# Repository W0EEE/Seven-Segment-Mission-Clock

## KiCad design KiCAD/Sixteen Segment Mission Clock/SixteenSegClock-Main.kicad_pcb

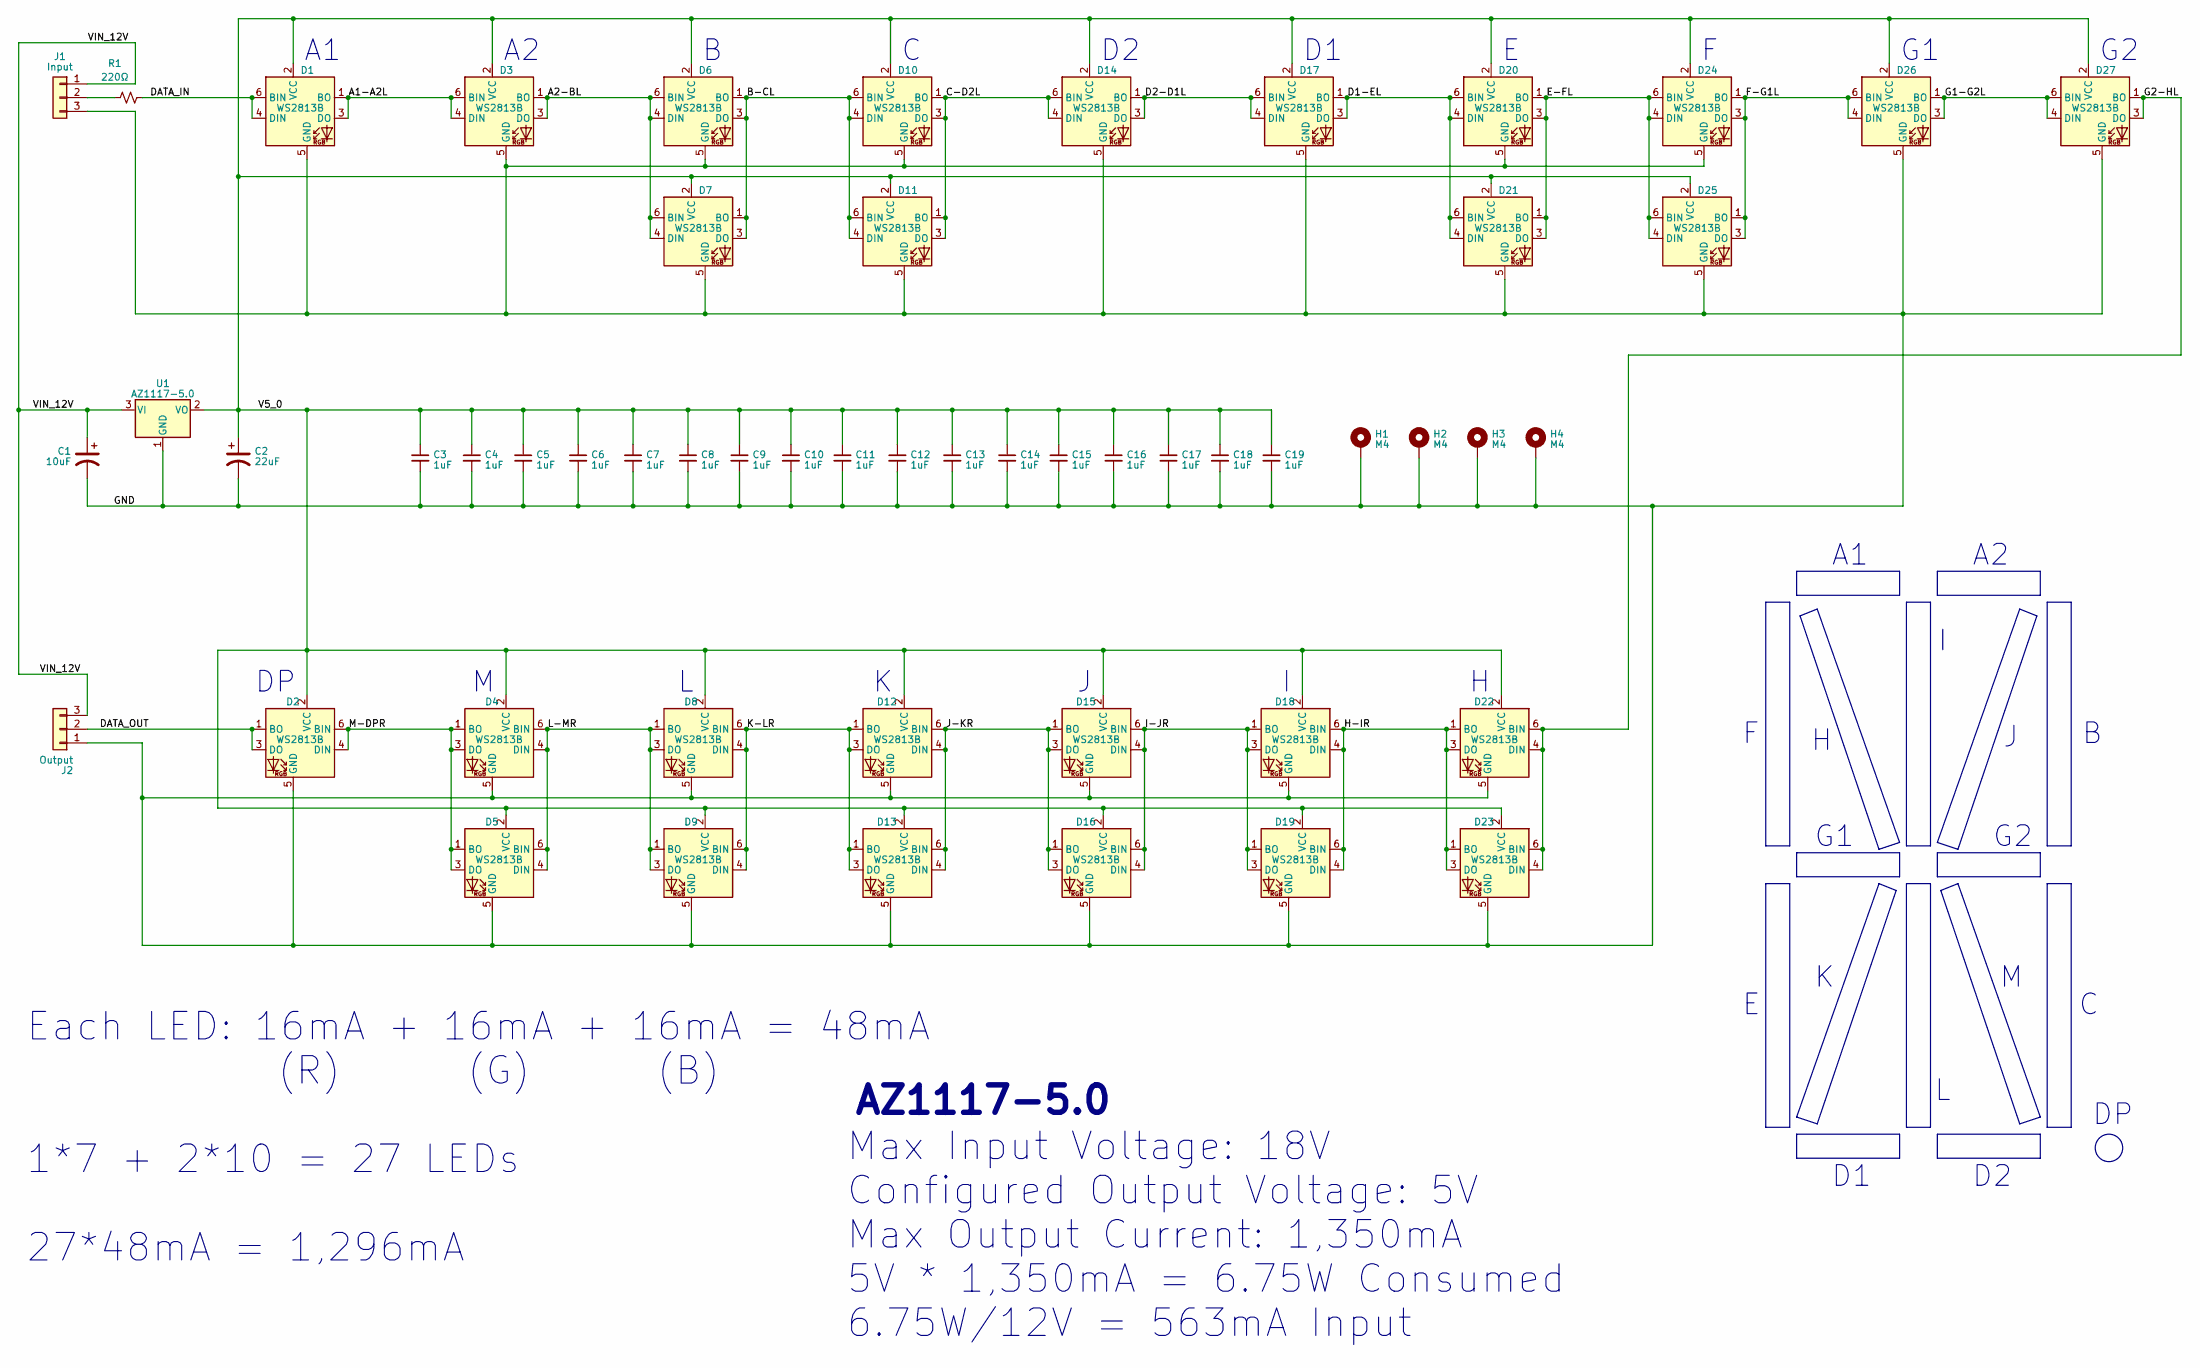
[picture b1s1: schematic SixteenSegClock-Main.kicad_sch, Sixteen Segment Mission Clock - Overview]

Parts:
C1: 10uF; C_0603_1608Metric_Pad1.08x0.95mm_HandSolder
C2: 22uF; C_0603_1608Metric_Pad1.08x0.95mm_HandSolder
C3, C4, C5, C6, C7, C8, C9, C10, C11, C12, C13, C14, C15, C16, C17, C18, C19: 1uF; C_0603_1608Metric_Pad1.08x0.95mm_HandSolder
D1, D2, D3, D4, D5, D6, D7, D8, D9, D10, D11, D12, D13, D14, D15, D16, D17, D18, D19, D20, D21, D22, D23, D24, D25, D26, D27: WS2813B; LED_WS2812_PLCC6_5.0x5.0mm_P1.6mm
H1, H2, H3, H4: M4; MountingHole_4.3mm_M4_DIN965_Pad
J1: Input; PinHeader_1x03_P2.54mm_Horizontal
J2: Output; PinHeader_1x03_P2.54mm_Horizontal
R1: 220Ω; R_0603_1608Metric_Pad0.98x0.95mm_HandSolder
U1: AZ1117-5.0; SOT-223-3_TabPin2

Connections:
/A1-A2L: D1.1 (BO), D1.3 (DO), D3.4 (DIN), D3.6 (BIN)
/A2-BL: D3.1 (BO), D3.3 (DO), D6.4 (DIN), D6.6 (BIN), D7.4 (DIN), D7.6 (BIN)
/B-CL: D6.1 (BO), D6.3 (DO), D7.1 (BO), D7.3 (DO), D10.4 (DIN), D10.6 (BIN), D11.4 (DIN), D11.6 (BIN)
/C-D2L: D10.1 (BO), D10.3 (DO), D11.1 (BO), D11.3 (DO), D14.4 (DIN), D14.6 (BIN)
/D1-EL: D17.1 (BO), D17.3 (DO), D20.4 (DIN), D20.6 (BIN), D21.4 (DIN), D21.6 (BIN)
/D2-D1L: D14.1 (BO), D14.3 (DO), D17.4 (DIN), D17.6 (BIN)
/DATA_IN: D1.4 (DIN), D1.6 (BIN), R1.2
/DATA_OUT: D2.1 (BO), D2.3 (DO), J2.2
/E-FL: D20.1 (BO), D20.3 (DO), D21.1 (BO), D21.3 (DO), D24.4 (DIN), D24.6 (BIN), D25.4 (DIN), D25.6 (BIN)
/F-G1L: D24.1 (BO), D24.3 (DO), D25.1 (BO), D25.3 (DO), D26.4 (DIN), D26.6 (BIN)
/G1-G2L: D26.1 (BO), D26.3 (DO), D27.4 (DIN), D27.6 (BIN)
/G2-HL: D22.4 (DIN), D22.6 (BIN), D23.4 (DIN), D23.6 (BIN), D27.1 (BO), D27.3 (DO)
/GND: C1.2, C2.2, C3.2, C4.2, C5.2, C6.2, C7.2, C8.2, C9.2, C10.2, C11.2, C12.2, C13.2, C14.2, C15.2, C16.2, C17.2, C18.2, C19.2, D1.5 (GND), D2.5 (GND), D3.5 (GND), D4.5 (GND), D5.5 (GND), D6.5 (GND), D7.5 (GND), D8.5 (GND), D9.5 (GND), D10.5 (GND), D11.5 (GND), D12.5 (GND), D13.5 (GND), D14.5 (GND), D15.5 (GND), D16.5 (GND), D17.5 (GND), D18.5 (GND), D19.5 (GND), D20.5 (GND), D21.5 (GND), D22.5 (GND), D23.5 (GND), D24.5 (GND), D25.5 (GND), D26.5 (GND), D27.5 (GND), H1.1, H2.1, H3.1, H4.1, J1.3, J2.1, U1.1 (GND)
/H-IR: D18.4 (DIN), D18.6 (BIN), D19.4 (DIN), D19.6 (BIN), D22.1 (BO), D22.3 (DO), D23.1 (BO), D23.3 (DO)
/I-JR: D15.4 (DIN), D15.6 (BIN), D16.4 (DIN), D16.6 (BIN), D18.1 (BO), D18.3 (DO), D19.1 (BO), D19.3 (DO)
/J-KR: D12.4 (DIN), D12.6 (BIN), D13.4 (DIN), D13.6 (BIN), D15.1 (BO), D15.3 (DO), D16.1 (BO), D16.3 (DO)
/K-LR: D8.4 (DIN), D8.6 (BIN), D9.4 (DIN), D9.6 (BIN), D12.1 (BO), D12.3 (DO), D13.1 (BO), D13.3 (DO)
/L-MR: D4.4 (DIN), D4.6 (BIN), D5.4 (DIN), D5.6 (BIN), D8.1 (BO), D8.3 (DO), D9.1 (BO), D9.3 (DO)
/M-DPR: D2.4 (DIN), D2.6 (BIN), D4.1 (BO), D4.3 (DO), D5.1 (BO), D5.3 (DO)
/V5_0: C2.1, C3.1, C4.1, C5.1, C6.1, C7.1, C8.1, C9.1, C10.1, C11.1, C12.1, C13.1, C14.1, C15.1, C16.1, C17.1, C18.1, C19.1, D1.2 (VCC), D2.2 (VCC), D3.2 (VCC), D4.2 (VCC), D5.2 (VCC), D6.2 (VCC), D7.2 (VCC), D8.2 (VCC), D9.2 (VCC), D10.2 (VCC), D11.2 (VCC), D12.2 (VCC), D13.2 (VCC), D14.2 (VCC), D15.2 (VCC), D16.2 (VCC), D17.2 (VCC), D18.2 (VCC), D19.2 (VCC), D20.2 (VCC), D21.2 (VCC), D22.2 (VCC), D23.2 (VCC), D24.2 (VCC), D25.2 (VCC), D26.2 (VCC), D27.2 (VCC), U1.2 (VO)
/VIN_12V: C1.1, J1.1, J2.3, U1.3 (VI)
unnamed: J1.2, R1.1

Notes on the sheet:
Max Input Voltage: 18V Configured Output Voltage: 5V Max Output Current: 1,350mA 5V * 1,350mA = 6.75W Consumed 6.75W/12V = 563mA Input
Each LED: 16mA + 16mA + 16mA = 48mA (R) (G) (B) 1*7 + 2*10 = 27 LEDs 27*48mA = 1,296mA
AZ1117-5.0

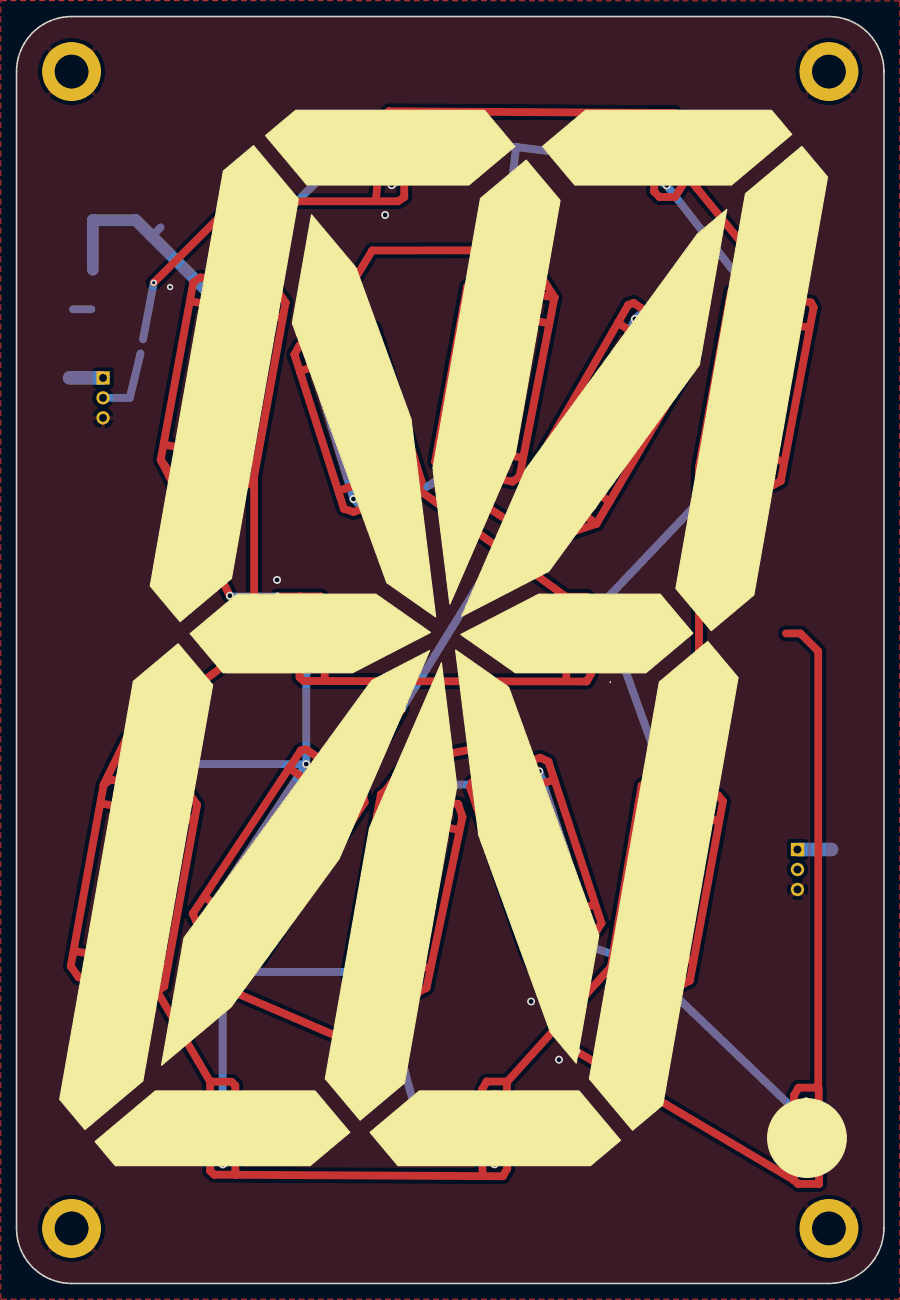
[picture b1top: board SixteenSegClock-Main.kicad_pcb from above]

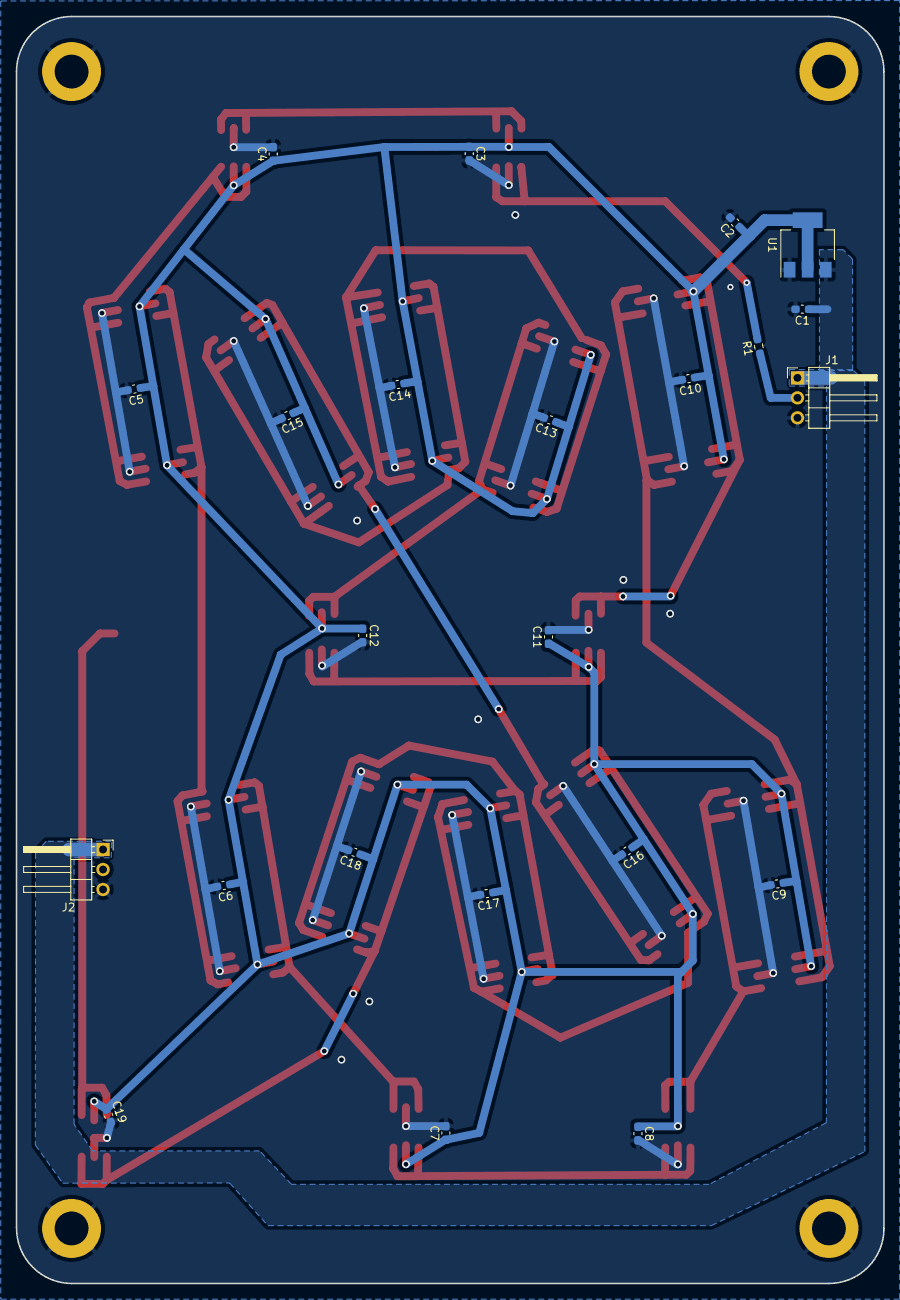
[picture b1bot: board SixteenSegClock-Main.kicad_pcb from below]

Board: 2 copper layers, 110.3 x 161.1 mm, 54 parts (23 on the bottom side), 22 nets.

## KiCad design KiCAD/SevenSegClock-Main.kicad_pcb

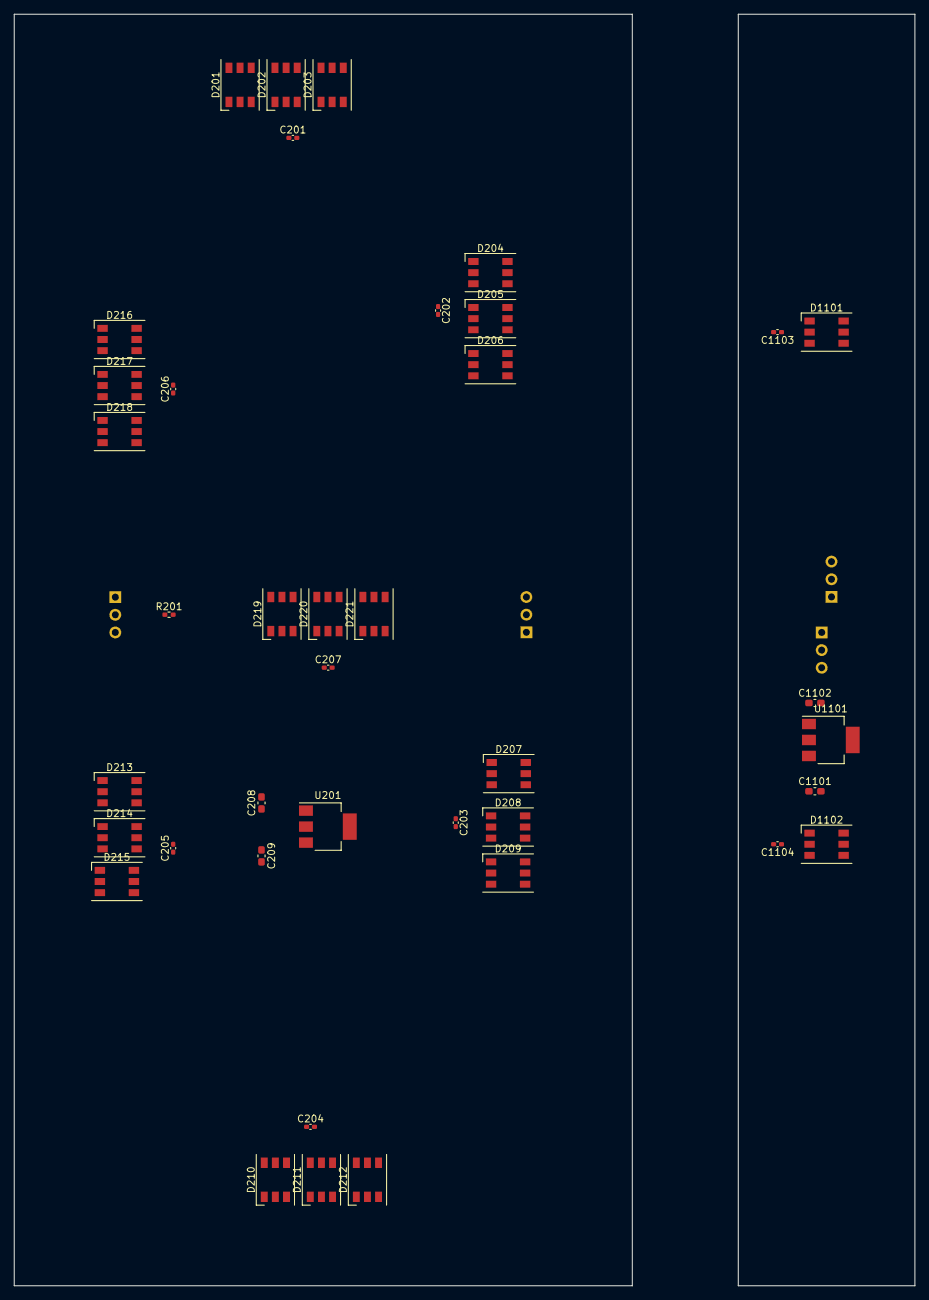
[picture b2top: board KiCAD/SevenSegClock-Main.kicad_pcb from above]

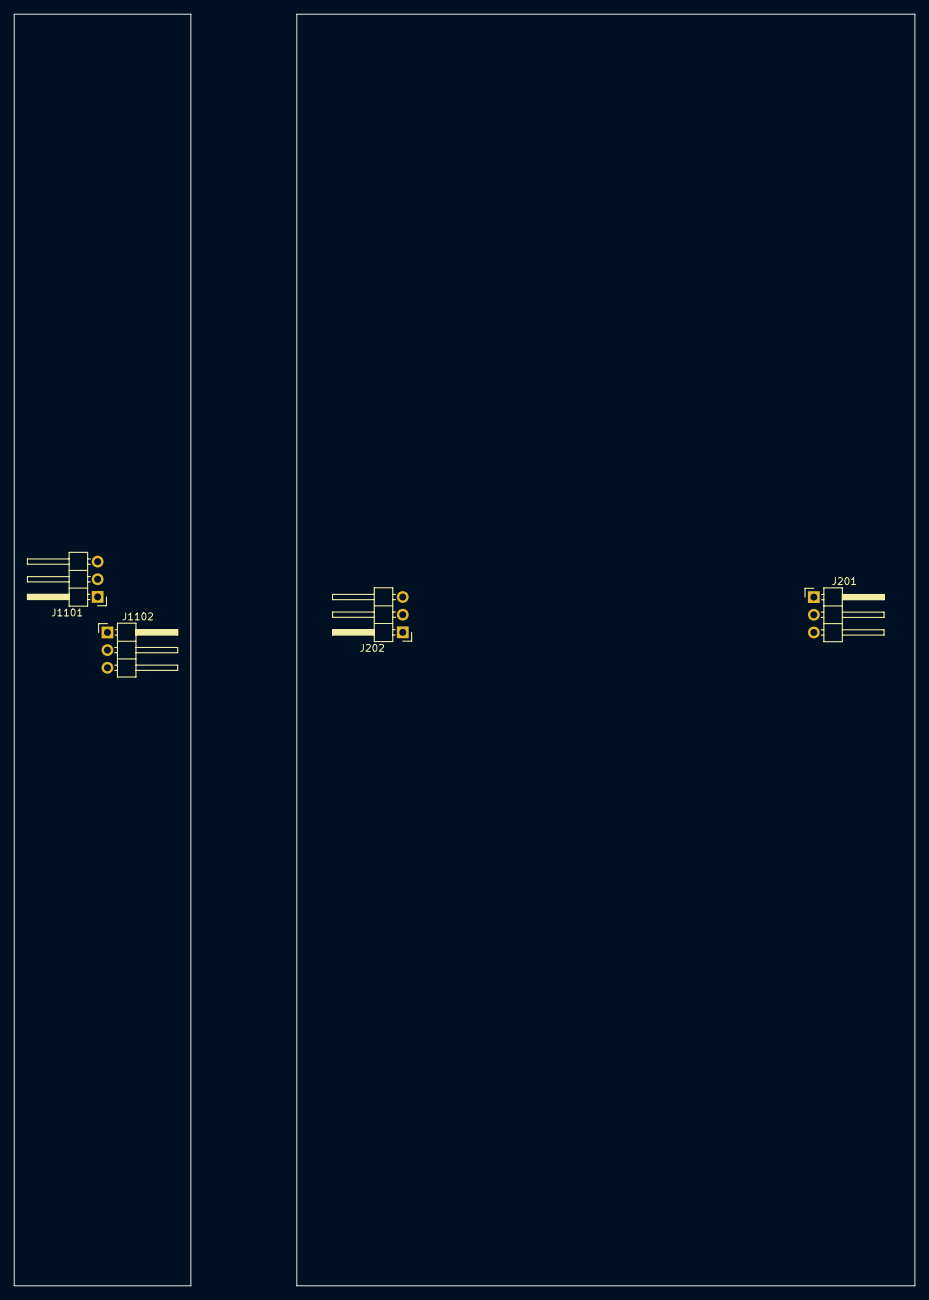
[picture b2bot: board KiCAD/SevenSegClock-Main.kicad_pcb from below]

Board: 2 copper layers, 129.5 x 182.9 mm, 43 parts (4 on the bottom side), 17 nets, no tracks yet.

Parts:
C201, C202, C203, C204, C205, C206, C207, C1103, C1104: 1uF; C_0402_1005Metric_Pad0.74x0.62mm_HandSolder
C208, C209, C1101, C1102: 10uF; C_0603_1608Metric_Pad1.08x0.95mm_HandSolder
D201, D202, D203, D204, D205, D206, D207, D208, D209, D210, D211, D212, D213, D214, D215, D216, D217, D218, D219, D220, D221, D1101, D1102: WS2813B; LED_WS2812_PLCC6_5.0x5.0mm_P1.6mm
J201: Input; PinHeader_1x03_P2.54mm_Horizontal
J202, J1101, J1102: Output; PinHeader_1x03_P2.54mm_Horizontal
R201: 220Ω; R_0402_1005Metric_Pad0.72x0.64mm_HandSolder
U201, U1101: AZ1117-5.0; SOT-223-3_TabPin2

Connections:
/Colon 1/DATA_IN: D1101.4 (DIN), D1101.6 (BIN), D1102.4 (DIN), D1102.6 (BIN), J1102.2
/Colon 1/DATA_OUT: D1101.1 (BO), D1101.3 (DO), D1102.1 (BO), D1102.3 (DO), J1101.2
/Colon 1/GND: C1101.2, C1102.2, C1103.2, C1104.2, D1101.5 (GND), D1102.5 (GND), J1101.3, J1102.3, U1101.1 (GND)
/Colon 1/V5_0: C1102.1, C1103.1, C1104.1, D1101.2 (VCC), D1102.2 (VCC), U1101.2 (VO)
/Colon 1/VIN_12V: C1101.1, J1101.1, J1102.1, U1101.3 (VI)
/Day 100s/A-B: D201.1 (BO), D201.3 (DO), D202.1 (BO), D202.3 (DO), D203.1 (BO), D203.3 (DO), D204.4 (DIN), D204.6 (BIN), D205.4 (DIN), D205.6 (BIN), D206.4 (DIN), D206.6 (BIN)
/Day 100s/B-C: D204.1 (BO), D204.3 (DO), D205.1 (BO), D205.3 (DO), D206.1 (BO), D206.3 (DO), D207.4 (DIN), D207.6 (BIN), D208.4 (DIN), D208.6 (BIN), D209.4 (DIN), D209.6 (BIN)
/Day 100s/C-D: D207.1 (BO), D207.3 (DO), D208.1 (BO), D208.3 (DO), D209.1 (BO), D209.3 (DO), D210.4 (DIN), D210.6 (BIN), D213.4 (DIN), D213.6 (BIN), D216.4 (DIN), D216.6 (BIN)
/Day 100s/D-E: D210.1 (BO), D210.3 (DO), D211.4 (DIN), D211.6 (BIN), D213.1 (BO), D213.3 (DO), D214.4 (DIN), D214.6 (BIN), D216.1 (BO), D216.3 (DO), D217.4 (DIN), D217.6 (BIN)
/Day 100s/DATA_IN: D201.4 (DIN), D201.6 (BIN), D202.4 (DIN), D202.6 (BIN), D203.4 (DIN), D203.6 (BIN), R201.2
/Day 100s/DATA_OUT: D219.1 (BO), D219.3 (DO), D220.1 (BO), D220.3 (DO), D221.1 (BO), D221.3 (DO), J202.2
/Day 100s/E-F: D211.1 (BO), D211.3 (DO), D212.4 (DIN), D212.6 (BIN), D214.1 (BO), D214.3 (DO), D215.4 (DIN), D215.6 (BIN), D217.1 (BO), D217.3 (DO), D218.4 (DIN), D218.6 (BIN)
/Day 100s/F-G: D212.1 (BO), D212.3 (DO), D215.1 (BO), D215.3 (DO), D218.1 (BO), D218.3 (DO), D219.4 (DIN), D219.6 (BIN), D220.4 (DIN), D220.6 (BIN), D221.4 (DIN), D221.6 (BIN)
/Day 100s/GND: C201.2, C202.2, C203.2, C204.2, C205.2, C206.2, C207.2, C208.2, C209.2, D201.5 (GND), D202.5 (GND), D203.5 (GND), D204.5 (GND), D205.5 (GND), D206.5 (GND), D207.5 (GND), D208.5 (GND), D209.5 (GND), D210.5 (GND), D211.5 (GND), D212.5 (GND), D213.5 (GND), D214.5 (GND), D215.5 (GND), D216.5 (GND), D217.5 (GND), D218.5 (GND), D219.5 (GND), D220.5 (GND), D221.5 (GND), J201.3, J202.3, U201.1 (GND)
/Day 100s/V5_0: C201.1, C202.1, C203.1, C204.1, C205.1, C206.1, C207.1, C208.1, D201.2 (VCC), D202.2 (VCC), D203.2 (VCC), D204.2 (VCC), D205.2 (VCC), D206.2 (VCC), D207.2 (VCC), D208.2 (VCC), D209.2 (VCC), D210.2 (VCC), D211.2 (VCC), D212.2 (VCC), D213.2 (VCC), D214.2 (VCC), D215.2 (VCC), D216.2 (VCC), D217.2 (VCC), D218.2 (VCC), D219.2 (VCC), D220.2 (VCC), D221.2 (VCC), U201.2 (VO)
/Day 100s/VIN_12V: C209.1, J201.1, J202.1, U201.3 (VI)
unnamed: J201.2, R201.1

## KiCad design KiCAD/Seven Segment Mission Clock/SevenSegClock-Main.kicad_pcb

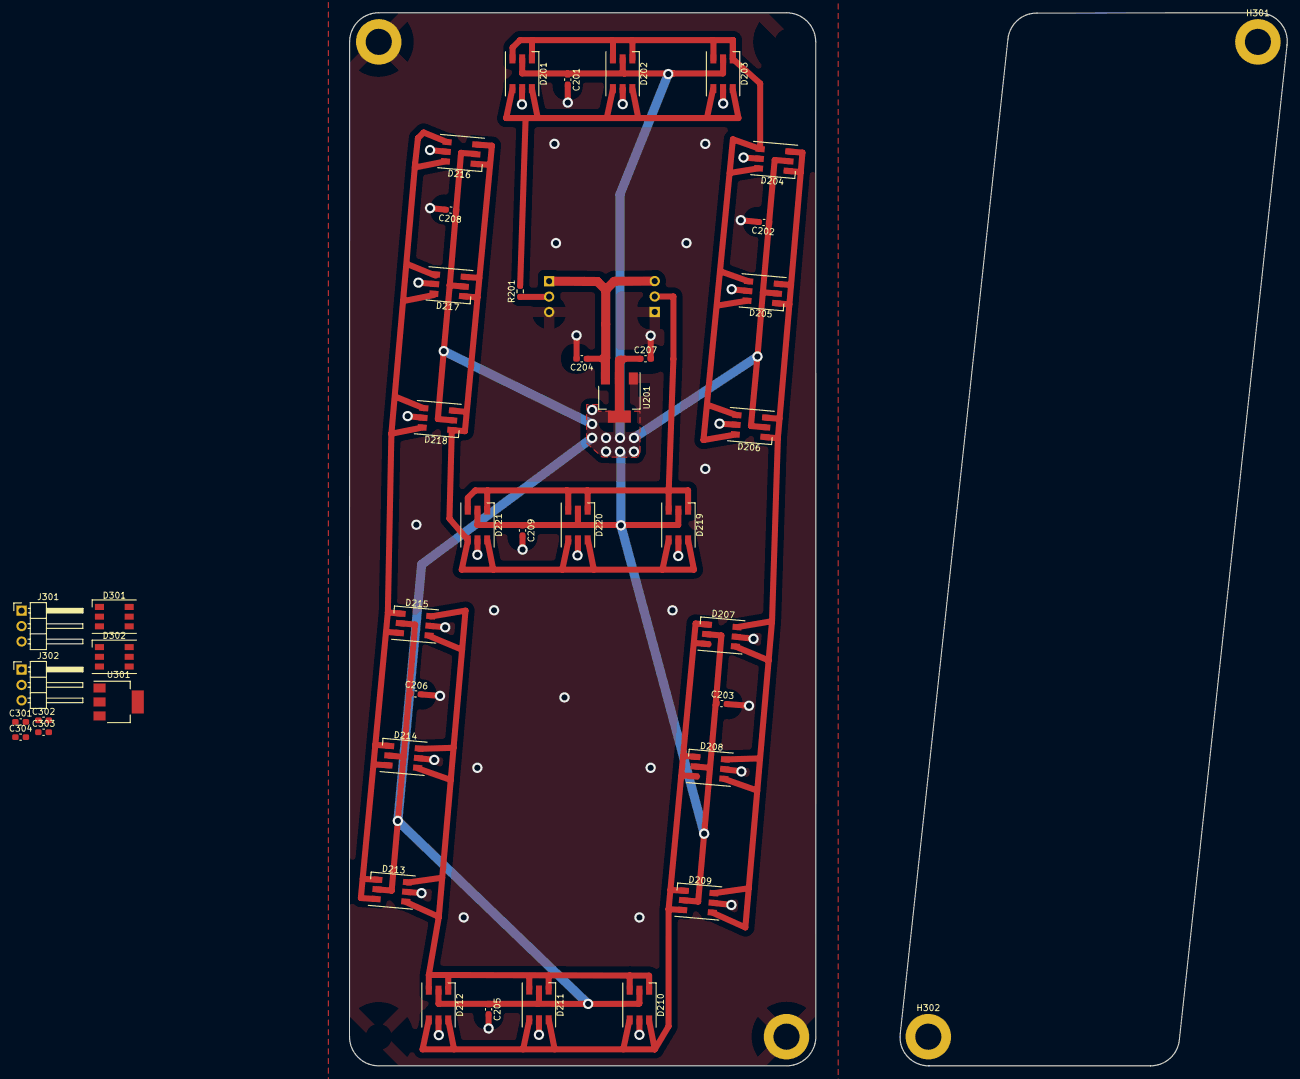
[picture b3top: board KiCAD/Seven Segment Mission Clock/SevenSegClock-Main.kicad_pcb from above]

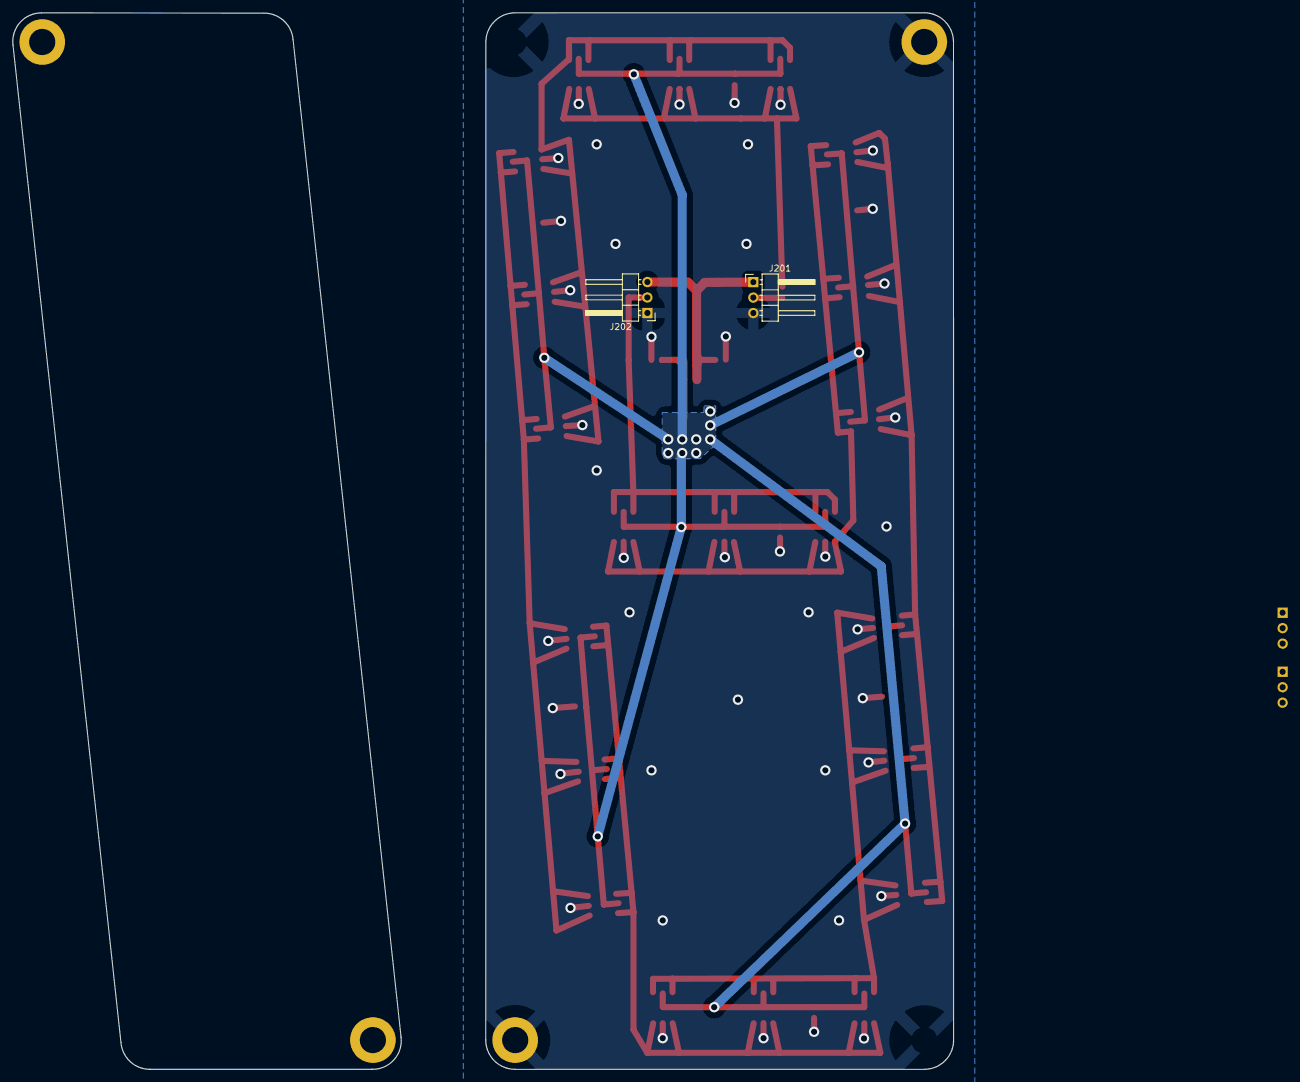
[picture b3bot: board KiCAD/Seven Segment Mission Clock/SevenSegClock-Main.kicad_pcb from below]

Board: 2 copper layers, 154.5 x 173.5 mm, 47 parts (2 on the bottom side), 17 nets.

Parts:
C201, C202, C203, C205, C206, C208, C209, C302, C303: 1uF; C_0603_1608Metric_Pad1.08x0.95mm_HandSolder
C204, C207, C301, C304: 10uF; C_0603_1608Metric_Pad1.08x0.95mm_HandSolder
D201, D202, D203, D204, D205, D206, D207, D208, D209, D210, D211, D212, D213, D214, D215, D216, D217, D218, D219, D220, D221, D301, D302: WS2813B; LED_WS2812_PLCC6_5.0x5.0mm_P1.6mm
H201, H202, H301, H302: M4; MountingHole_4.3mm_M4_DIN965_Pad
J201: Input; PinHeader_1x03_P2.54mm_Horizontal
J202, J301, J302: Output; PinHeader_1x03_P2.54mm_Horizontal
R201: 220Ω; R_0603_1608Metric_Pad0.98x0.95mm_HandSolder
U201, U301: AZ1117-5.0; SOT-223-3_TabPin2

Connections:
/Colon/DATA_IN: D301.4 (DIN), D301.6 (BIN), D302.4 (DIN), D302.6 (BIN), J301.2
/Colon/DATA_OUT: D301.1 (BO), D301.3 (DO), D302.1 (BO), D302.3 (DO), J302.2
/Colon/GND: C301.2, C302.2, C303.2, C304.2, D301.5 (GND), D302.5 (GND), H301.1, H302.1, J301.3, J302.3, U301.1 (GND)
/Colon/V5_0: C302.1, C303.1, C304.1, D301.2 (VCC), D302.2 (VCC), U301.2 (VO)
/Colon/VIN_12V: C301.1, J301.1, J302.1, U301.3 (VI)
/Seven Segment Digit/A-B: D201.1 (BO), D201.3 (DO), D202.1 (BO), D202.3 (DO), D203.1 (BO), D203.3 (DO), D204.4 (DIN), D204.6 (BIN), D205.4 (DIN), D205.6 (BIN), D206.4 (DIN), D206.6 (BIN)
/Seven Segment Digit/B-C: D204.1 (BO), D204.3 (DO), D205.1 (BO), D205.3 (DO), D206.1 (BO), D206.3 (DO), D207.4 (DIN), D207.6 (BIN), D208.4 (DIN), D208.6 (BIN), D209.4 (DIN), D209.6 (BIN)
/Seven Segment Digit/C-D: D207.1 (BO), D207.3 (DO), D208.1 (BO), D208.3 (DO), D209.1 (BO), D209.3 (DO), D210.4 (DIN), D210.6 (BIN), D211.4 (DIN), D211.6 (BIN), D212.4 (DIN), D212.6 (BIN)
/Seven Segment Digit/D-E: D210.1 (BO), D210.3 (DO), D211.1 (BO), D211.3 (DO), D212.1 (BO), D212.3 (DO), D213.4 (DIN), D213.6 (BIN), D214.4 (DIN), D214.6 (BIN), D215.4 (DIN), D215.6 (BIN)
/Seven Segment Digit/DATA_IN: D201.4 (DIN), D201.6 (BIN), D202.4 (DIN), D202.6 (BIN), D203.4 (DIN), D203.6 (BIN), R201.2
/Seven Segment Digit/DATA_OUT: D219.1 (BO), D219.3 (DO), D220.1 (BO), D220.3 (DO), D221.1 (BO), D221.3 (DO), J202.2
/Seven Segment Digit/E-F: D213.1 (BO), D213.3 (DO), D214.1 (BO), D214.3 (DO), D215.1 (BO), D215.3 (DO), D216.4 (DIN), D216.6 (BIN), D217.4 (DIN), D217.6 (BIN), D218.4 (DIN), D218.6 (BIN)
/Seven Segment Digit/F-G: D216.1 (BO), D216.3 (DO), D217.1 (BO), D217.3 (DO), D218.1 (BO), D218.3 (DO), D219.4 (DIN), D219.6 (BIN), D220.4 (DIN), D220.6 (BIN), D221.4 (DIN), D221.6 (BIN)
/Seven Segment Digit/GND: C201.2, C202.2, C203.2, C204.2, C205.2, C206.2, C207.2, C208.2, C209.2, D201.5 (GND), D202.5 (GND), D203.5 (GND), D204.5 (GND), D205.5 (GND), D206.5 (GND), D207.5 (GND), D208.5 (GND), D209.5 (GND), D210.5 (GND), D211.5 (GND), D212.5 (GND), D213.5 (GND), D214.5 (GND), D215.5 (GND), D216.5 (GND), D217.5 (GND), D218.5 (GND), D219.5 (GND), D220.5 (GND), D221.5 (GND), H201.1, H202.1, J201.3, J202.1, U201.1 (GND)
/Seven Segment Digit/V5_0: C201.1, C202.1, C203.1, C205.1, C206.1, C207.1, C208.1, C209.1, D201.2 (VCC), D202.2 (VCC), D203.2 (VCC), D204.2 (VCC), D205.2 (VCC), D206.2 (VCC), D207.2 (VCC), D208.2 (VCC), D209.2 (VCC), D210.2 (VCC), D211.2 (VCC), D212.2 (VCC), D213.2 (VCC), D214.2 (VCC), D215.2 (VCC), D216.2 (VCC), D217.2 (VCC), D218.2 (VCC), D219.2 (VCC), D220.2 (VCC), D221.2 (VCC), U201.2 (VO)
/Seven Segment Digit/VIN_12V: C204.1, J201.1, J202.3, U201.3 (VI)
unnamed: J201.2, R201.1

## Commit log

2023-10-23 Created initial schematic
2023-10-23 Added parts list
2023-11-10 Initial PCB layout for 7-seg digits
    I realize now that the PCB for the digits needs to be slanted, otherwise the colon pcb won't fit next to it, grumble
2023-11-10 Reduced 7-seg mounting holes to 2
2023-11-22 Added files for sixteen segment display
2023-11-22 Created Sixteen Segment Schematic
2023-11-22 Fixed regulator math, added to sixteen segment display
2023-11-22 Added decoupling caps
2023-11-22 Added outline to pcb
2023-11-22 Added Fusion file for 16-seg clock
2023-11-22 Placed LEDs
2023-11-22 Initial routings
2023-11-22 Routed all components
2023-11-22 Corrected 3D model
2023-11-24 Rounded corners
2023-11-25 New 3D Model
2023-12-05 Finalized PCB Routing & Artwork
2023-12-05 Generated Gerbers
2023-12-06 add 32u4 and w5100
2023-12-06 Renamed 22uF to 10uF
    Due to component availability
